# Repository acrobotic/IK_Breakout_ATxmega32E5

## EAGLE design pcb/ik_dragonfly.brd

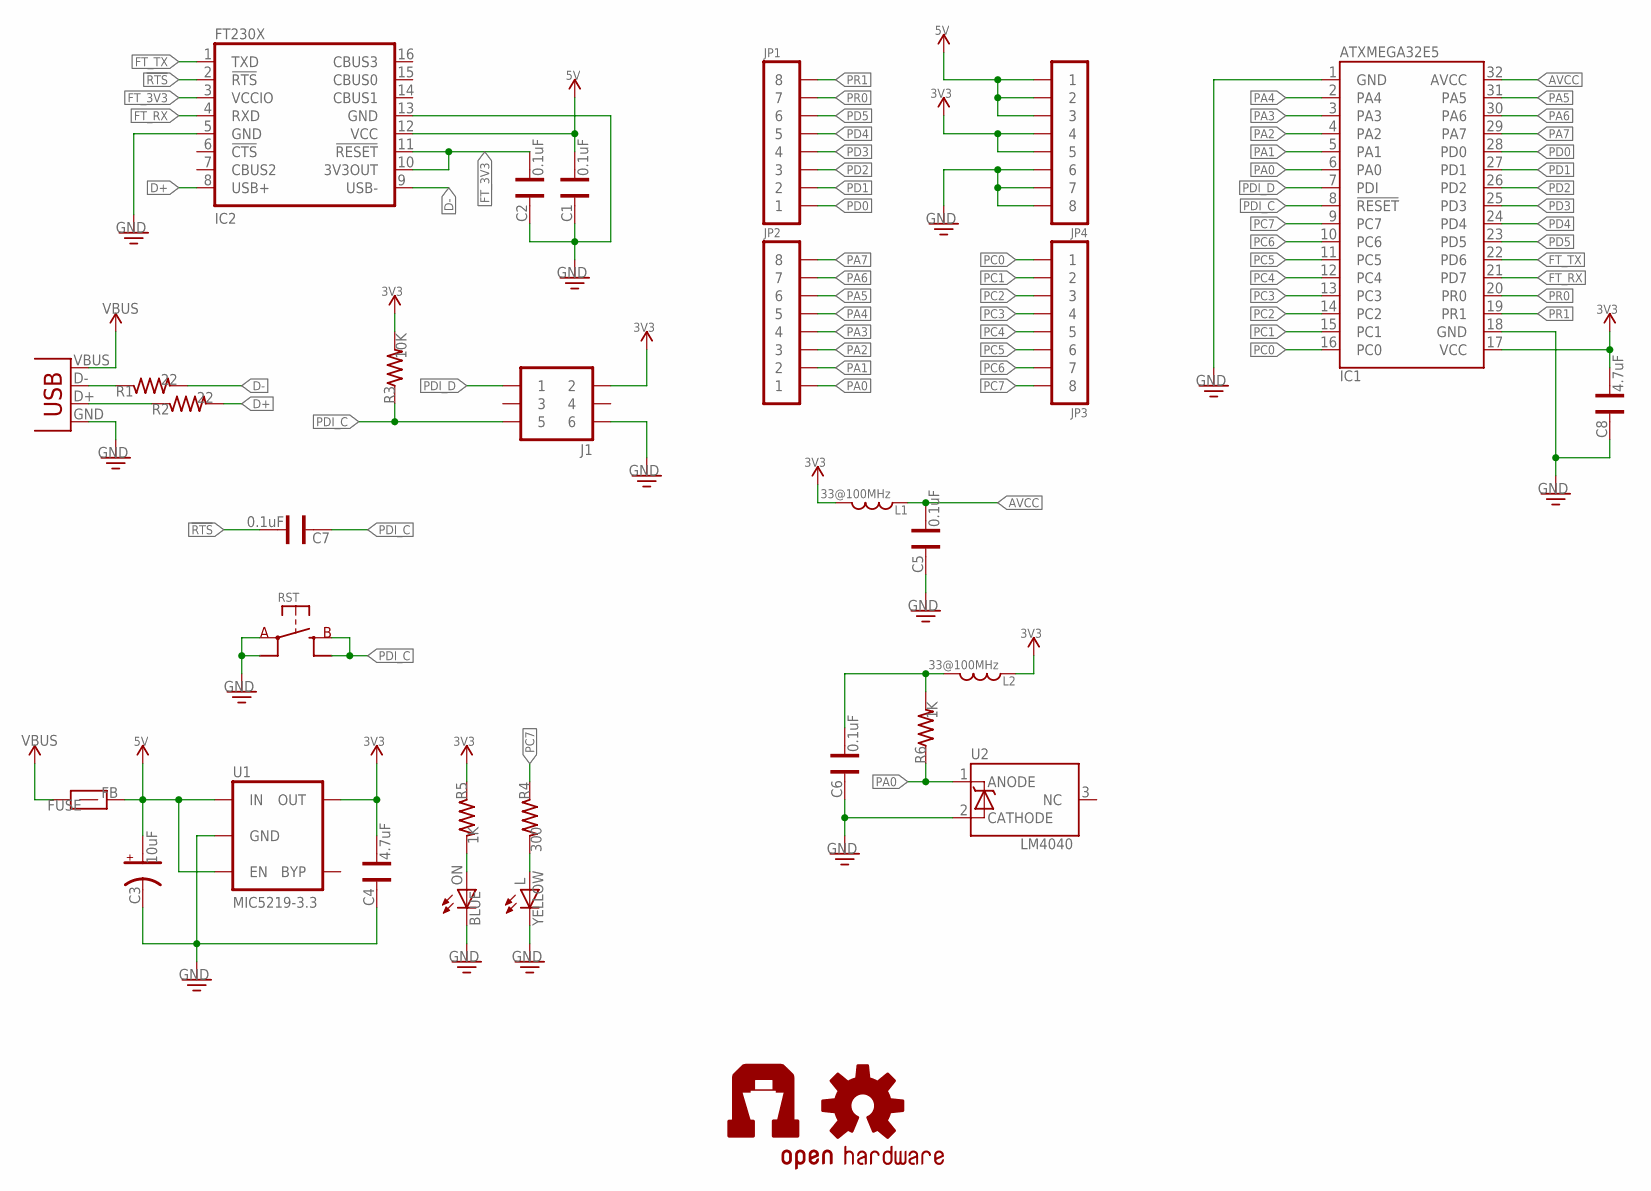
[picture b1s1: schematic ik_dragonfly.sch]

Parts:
C1, C2, C5, C6, C7: 0.1uF; CAP-0603
C3: 10uF; CAP-POL-EIA3216
C4, C8: 4.7uF; CAP-0603
FUSE: FB; FB-0603
IC1: ATXMEGA32E5; TQFP32-08
IC2: FT230X; SSOP-16-FTDI
J1: 2X03
JP1, JP2, JP3, JP4: 1X08NOFIRST; 1X08-NOFIRST
L: YELLOW; LED-0603
L1, L2: 33@100MHz; IND-0603
LOGO1: OSHW-LOGOS; OSHW-LOGO-S
ON: BLUE; LED-0603
R1, R2: 22; RES-0603
R3: 10K; RES-0603
R4: 300; RES-0603
R5, R6: 1K; RES-0603
RST: SW-SPSTSMD035X030; SW-SPST-SMD035X030
U1: MIC5219-3.3; SOT23-5
U2: LM4040; SOT23-3
U$3: AI-LOGOXS; AI-LOGO-XS
USB1: USBMICROB-TH; USB-MICROB-TH

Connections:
3V3: C4.1, C8.1, IC1.17 (VCC), J1.2, JP4.4, JP4.5, L1.1, L2.2, R3.2, R5.1, U1.5 (OUT)
5V: C1.1, C3.A, FUSE.2, IC2.12 (VCC), JP4.1, JP4.2, JP4.3, U1.1 (IN), U1.3 (EN)
!RTS: C7.1, IC2.2 (!RTS)
AVCC: C5.1, IC1.32 (AVCC), L1.2
D+: IC2.8 (USB+), R2.2
D-: IC2.9 (USB-), R1.2
FT_3V3: C2.1, IC2.3 (VCCIO), IC2.10 (3V3OUT), IC2.11 (!RESET)
FT_RX: IC1.21 (PD7), IC2.4 (RXD)
FT_TX: IC1.22 (PD6), IC2.1 (TXD)
GND: C1.2, C2.2, C3.C, C4.2, C5.2, C6.2, C8.2, IC1.1 (GND), IC1.18 (GND), IC2.5 (GND), IC2.13 (GND), J1.6, JP4.6, JP4.7, JP4.8, L.C, ON.C, RST.1 (A), RST.2 (A), U1.2 (GND), U2.2 (CATHODE), USB1.GND
unnamed: R1.1, USB1.D-
unnamed: R2.1, USB1.D+
unnamed: L.A, R4.2
unnamed: ON.A, R5.2
unnamed: C6.1, L2.1, R6.2
PA0: IC1.6 (PA0), JP2.1, R6.1, U2.1 (ANODE)
PA1: IC1.5 (PA1), JP2.2
PA2: IC1.4 (PA2), JP2.3
PA3: IC1.3 (PA3), JP2.4
PA4: IC1.2 (PA4), JP2.5
PA5: IC1.31 (PA5), JP2.6
PA6: IC1.30 (PA6), JP2.7
PA7: IC1.29 (PA7), JP2.8
PC0: IC1.16 (PC0), JP3.1
PC1: IC1.15 (PC1), JP3.2
PC2: IC1.14 (PC2), JP3.3
PC3: IC1.13 (PC3), JP3.4
PC4: IC1.12 (PC4), JP3.5
PC5: IC1.11 (PC5), JP3.6
PC6: IC1.10 (PC6), JP3.7
PC7: IC1.9 (PC7), JP3.8, R4.1
PD0: IC1.28 (PD0), JP1.1
PD1: IC1.27 (PD1), JP1.2
PD2: IC1.26 (PD2), JP1.3
PD3: IC1.25 (PD3), JP1.4
PD4: IC1.24 (PD4), JP1.5
PD5: IC1.23 (PD5), JP1.6
PDI_C: C7.2, IC1.8 (!RESET), J1.5, R3.1, RST.3 (B), RST.4 (B)
PDI_D: IC1.7 (PDI), J1.1
PR0: IC1.20 (PR0), JP1.7
PR1: IC1.19 (PR1), JP1.8
VBUS: FUSE.1, USB1.VBUS

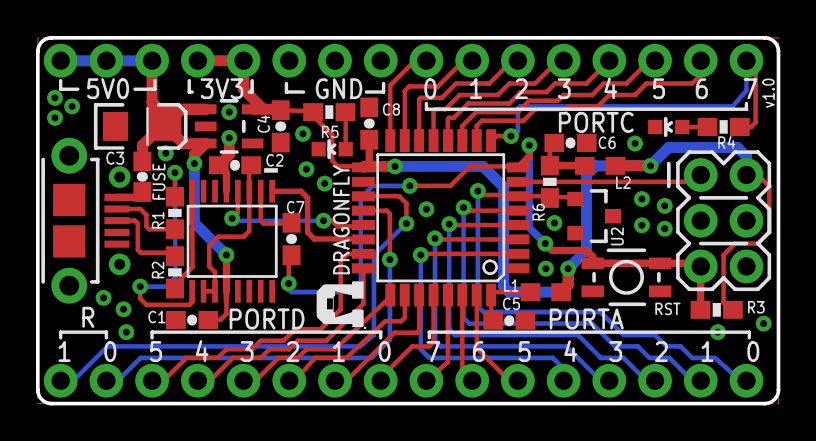
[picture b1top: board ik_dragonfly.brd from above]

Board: 2 copper layers, 41.1 x 20.3 mm, 32 parts (1 on the bottom side), 42 nets.

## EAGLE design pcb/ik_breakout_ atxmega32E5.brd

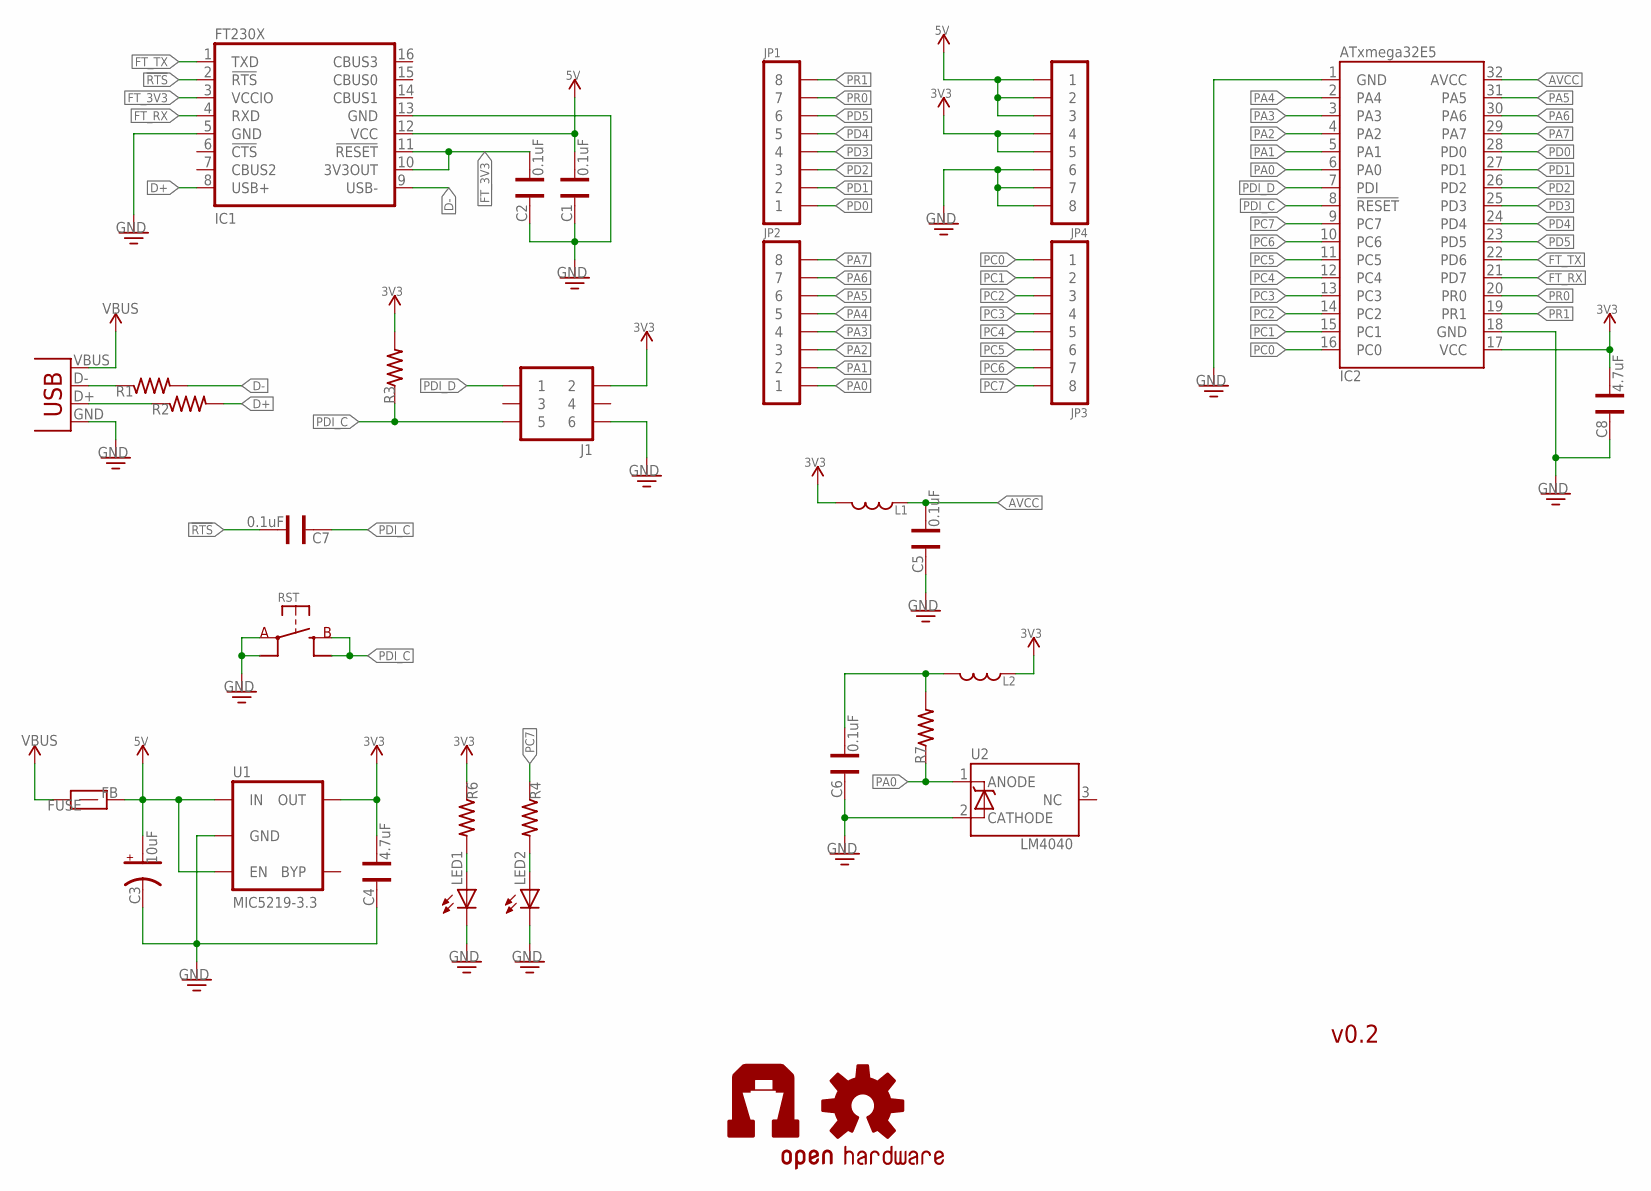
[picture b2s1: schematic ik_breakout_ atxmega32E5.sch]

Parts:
C1, C2, C5, C6, C7: 0.1uF; CAP-0603
C3: 10uF; CAP-POL-EIA3216
C4, C8: 4.7uF; CAP-0603
FUSE: FB; FB-0603
IC1: FT230X; SSOP-16-FTDI
IC2: ATXMEGA32E5; TQFP32-08
J1: 2X03
JP1, JP2, JP3, JP4: 1X08NOFIRST; 1X08-NOFIRST
L1, L2: IND0603; IND-0603
LED1, LED2: LED0603; LED-0603
LOGO1: OSHW-LOGOS; OSHW-LOGO-S
R1, R2, R3, R4, R6, R7: RES0603; RES-0603
RST: SW-SPSTSMD03X026; SW-SPST-SMD03X026
U1: MIC5219-3.3; SOT23-5
U2: LM4040; SOT23-3
U$3: AI-LOGOXS; AI-LOGO-XS
USB1: USBMICROB-TH; USB-MICROB-TH

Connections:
3V3: C4.1, C8.1, IC2.17 (VCC), J1.2, JP4.4, JP4.5, L1.1, L2.2, R3.2, R6.1, U1.5 (OUT)
5V: C1.1, C3.A, FUSE.2, IC1.12 (VCC), JP4.1, JP4.2, JP4.3, U1.1 (IN), U1.3 (EN)
!RTS: C7.1, IC1.2 (!RTS)
AVCC: C5.1, IC2.32 (AVCC), L1.2
D+: IC1.8 (USB+), R2.2
D-: IC1.9 (USB-), R1.2
FT_3V3: C2.1, IC1.3 (VCCIO), IC1.10 (3V3OUT), IC1.11 (!RESET)
FT_RX: IC1.4 (RXD), IC2.21 (PD7)
FT_TX: IC1.1 (TXD), IC2.22 (PD6)
GND: C1.2, C2.2, C3.C, C4.2, C5.2, C6.2, C8.2, IC1.5 (GND), IC1.13 (GND), IC2.1 (GND), IC2.18 (GND), J1.6, JP4.6, JP4.7, JP4.8, LED1.C, LED2.C, RST.1 (A), RST.2 (A), U1.2 (GND), U2.2 (CATHODE), USB1.GND
unnamed: R1.1, USB1.D-
unnamed: R2.1, USB1.D+
unnamed: LED2.A, R4.2
unnamed: LED1.A, R6.2
unnamed: C6.1, L2.1, R7.2
PA0: IC2.6 (PA0), JP2.1, R7.1, U2.1 (ANODE)
PA1: IC2.5 (PA1), JP2.2
PA2: IC2.4 (PA2), JP2.3
PA3: IC2.3 (PA3), JP2.4
PA4: IC2.2 (PA4), JP2.5
PA5: IC2.31 (PA5), JP2.6
PA6: IC2.30 (PA6), JP2.7
PA7: IC2.29 (PA7), JP2.8
PC0: IC2.16 (PC0), JP3.1
PC1: IC2.15 (PC1), JP3.2
PC2: IC2.14 (PC2), JP3.3
PC3: IC2.13 (PC3), JP3.4
PC4: IC2.12 (PC4), JP3.5
PC5: IC2.11 (PC5), JP3.6
PC6: IC2.10 (PC6), JP3.7
PC7: IC2.9 (PC7), JP3.8, R4.1
PD0: IC2.28 (PD0), JP1.1
PD1: IC2.27 (PD1), JP1.2
PD2: IC2.26 (PD2), JP1.3
PD3: IC2.25 (PD3), JP1.4
PD4: IC2.24 (PD4), JP1.5
PD5: IC2.23 (PD5), JP1.6
PDI_C: C7.2, IC2.8 (!RESET), J1.5, R3.1, RST.3 (B), RST.4 (B)
PDI_D: IC2.7 (PDI), J1.1
PR0: IC2.20 (PR0), JP1.7
PR1: IC2.19 (PR1), JP1.8
VBUS: FUSE.1, USB1.VBUS

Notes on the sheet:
v0.2

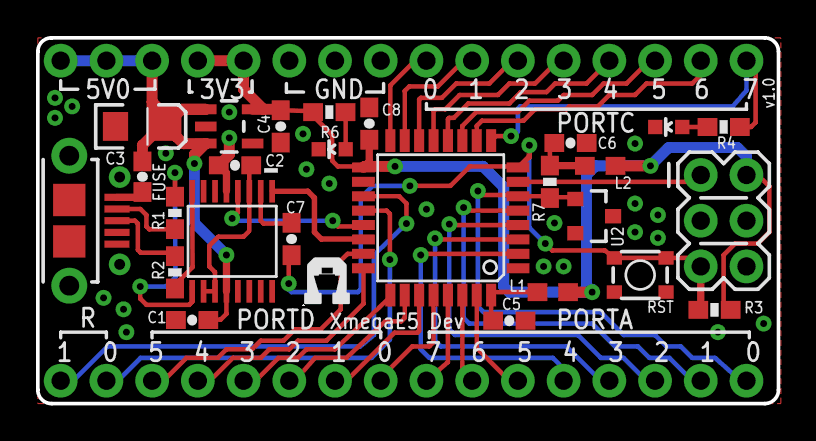
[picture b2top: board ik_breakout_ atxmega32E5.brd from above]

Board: 2 copper layers, 41.1 x 20.3 mm, 32 parts (1 on the bottom side), 42 nets.

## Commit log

2014-08-21 revised version
2014-08-21 oops. committed from /pcb/fab/gerbers folder.
2014-08-21 changed LM4040 to include part on Ai_Power library
2014-08-22 updated BOM
2014-08-23 finished BOM
2014-08-23 finished (for reals) BOM
2014-08-26 minor revision
2014-09-03 updating pdf
2014-09-05 styling BOM
2014-09-05 better pricing options on BOM

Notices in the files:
parts and their libraries:
SparkFun-Aesthetics: Licensing: CC v3.0 Share-Alike You are welcome to use this library for commercial purposes.
